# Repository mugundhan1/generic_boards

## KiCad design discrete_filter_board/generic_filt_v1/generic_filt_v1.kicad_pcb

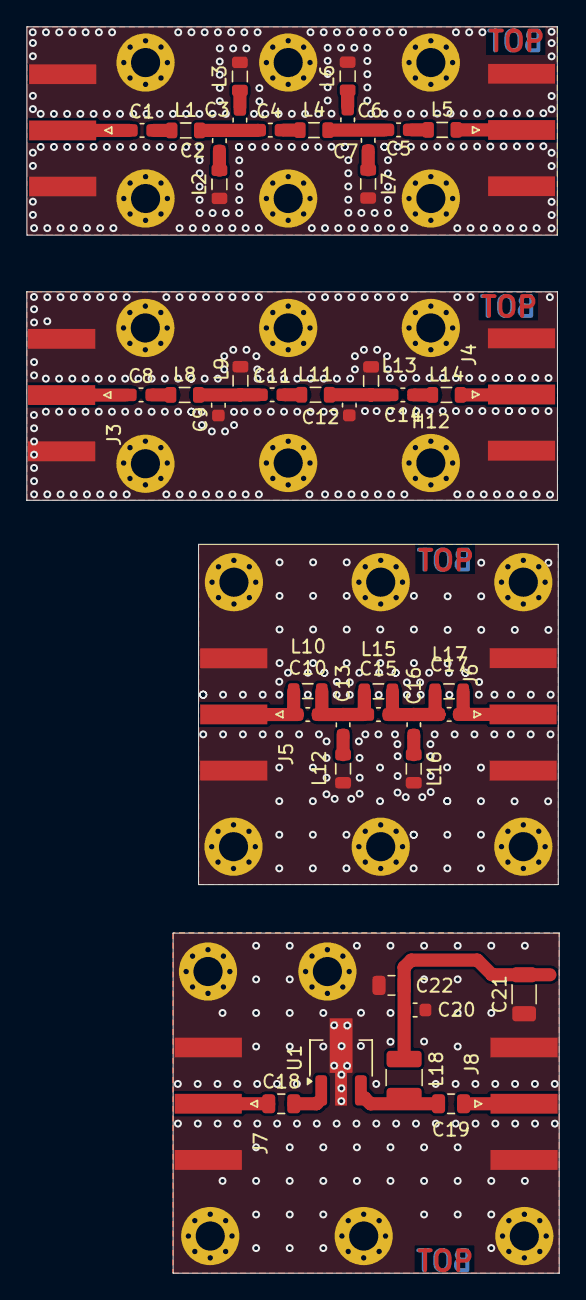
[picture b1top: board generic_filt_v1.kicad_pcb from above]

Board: 2 copper layers, 40.3 x 94.2 mm, 72 parts (0 on the bottom side), 30 nets.

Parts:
C1, C2, C3, C4, C5, C6, C7, C8, C9, C10, C11, C12, C13, C14, C15, C16, C17: C_Small; C_0603_1608Metric
C18, C19: 0.01 u; C_0805_2012Metric
C20: 0.1u; C_0603_1608Metric
C21: 10u; C_1206_3216Metric
C22: 1 u; C_0805_2012Metric
H1, H2, H3, H4, H5, H6, H7, H8, H9, H10, H11, H12, H13, H14, H15, H16, H17, H18, H19, H20, H21, H22, H23: MountingHole_Pad; MountingHole_2.2mm_M2_Pad_Via
J1, J2, J3, J4, J5, J6, J7, J8: Conn_Coaxial; SMA_Amphenol_132289_EdgeMount
L1, L2, L3, L4, L5, L6, L7, L8, L9, L10, L11, L12, L13, L14, L15, L16, L17: L_Small; L_0805_2012Metric
L18: 10 uH; L_1210_3225Metric
U1: PGA-103+; SOT-89-3_Handsoldering

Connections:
+5V: C20.2, C21.2, C22.2, L18.1
GND: C9.1, C12.1, C20.1, C21.1, C22.1, H1.1, H2.1, H3.1, H4.1, H5.1, H6.1, H7.1, H8.1, H9.1, H10.1, H11.1, H12.1, H13.1, H14.1, H15.1, H16.1, H17.1, H18.1, H19.1, H20.1, H21.1, H22.1, H23.1, J1.2 (Ext), J2.2 (Ext), J3.2 (Ext), J4.2 (Ext), J5.2 (Ext), J6.2 (Ext), J7.2 (Ext), J8.2 (Ext), L2.2, L3.2, L6.2, L7.2, L9.2, L12.2, L13.2, L16.2, U1.2 (GROUND)
unnamed: C1.2, L1.1
unnamed: C2.1, L2.1
unnamed: C2.2, C3.2, C4.1, L1.2
unnamed: C3.1, L3.1
unnamed: C4.2, L4.1
unnamed: C5.1, C6.2, C7.2, L4.2
unnamed: C5.2, L5.1
unnamed: C6.1, L6.1
unnamed: C7.1, L7.1
unnamed: C8.2, L8.1
unnamed: C10.2, C13.2, C15.1, L10.2, L15.1
unnamed: C9.2, C11.1, L8.2, L9.1
unnamed: C11.2, L11.1
unnamed: C12.2, C14.1, L11.2, L13.1
unnamed: C13.1, L12.1
unnamed: C14.2, L14.1
unnamed: C15.2, C16.2, C17.1, L15.2, L17.1
unnamed: C16.1, L16.1
unnamed: J1.1 (In), L5.2
unnamed: C1.1, J2.1 (In)
unnamed: C8.1, J3.1 (In)
unnamed: J4.1 (In), L14.2
unnamed: C10.1, J5.1 (In), L10.1
unnamed: C17.2, J6.1 (In), L17.2
unnamed: C18.1, J7.1 (In)
unnamed: C19.2, J8.1 (In)
unnamed: C18.2, U1.1 (RF-IN)
unnamed: C19.1, L18.2, U1.3 (RF-OUT/DC-IN)

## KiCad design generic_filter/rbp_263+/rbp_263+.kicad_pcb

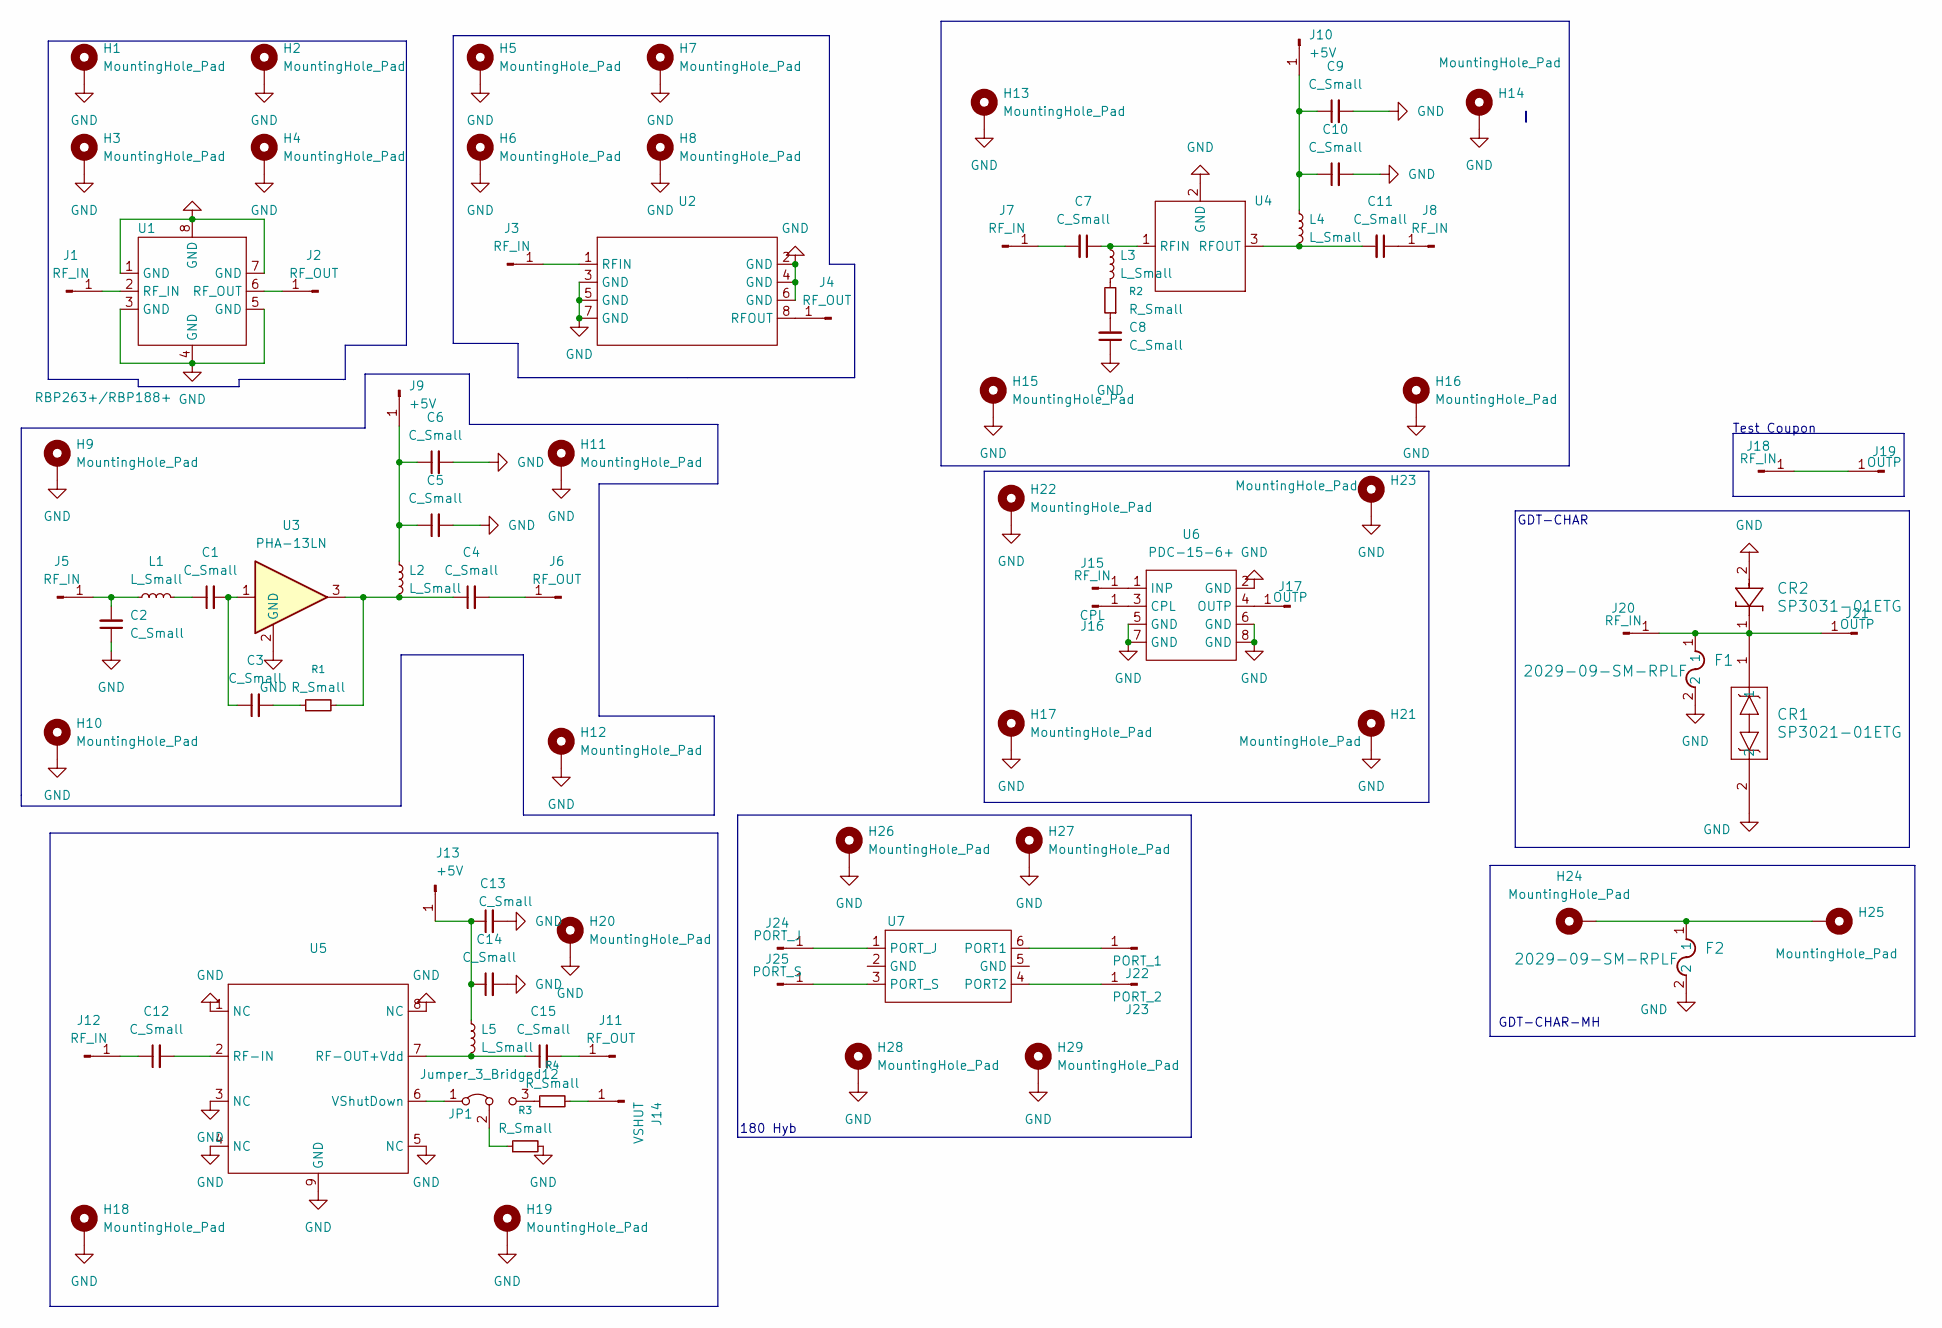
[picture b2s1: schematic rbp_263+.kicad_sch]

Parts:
C1, C2, C3, C4, C5, C7, C8, C10, C11, C12, C14, C15: C_Small; C_0603_1608Metric_Pad1.08x0.95mm_HandSolder
C6, C9, C13: C_Small; C_0805_2012Metric_Pad1.18x1.45mm_HandSolder
CR1: SP3021-01ETG; SOD882_LTF
CR2: SP3031-01ETG; SOD882_LTF-L
F1, F2: 2029-09-SM-RPLF; FUSE_2029-09-SM-RPLF_BRN
H1, H2, H3, H4, H5, H6, H7, H8, H9, H10, H11, H12, H13, H14, H15, H16, H17, H18, H19, H20, H21, H22, H23, H26, H27, H28, H29: MountingHole_Pad; MountingHole_2.2mm_M2_DIN965_Pad
H24, H25: MountingHole_Pad; MountingHole_2.7mm_M2.5_DIN965_Pad_TopBottom
J1, J3, J5, J7, J8, J12, J15, J18, J20: RF_IN; RF_SMA_Edge_PanelMount
J2, J4, J6, J11: RF_OUT; RF_SMA_Edge_PanelMount
J9, J10, J13: +5V; RF_SMA_Edge_PanelMount
J14: VSHUT; RF_SMA_Edge_PanelMount
J16: CPL; RF_SMA_Edge_PanelMount
J17, J19, J21: OUTP; RF_SMA_Edge_PanelMount
J22: PORT_1; RF_SMA_Edge_PanelMount
J23: PORT_2; RF_SMA_Edge_PanelMount
J24: PORT_J; RF_SMA_Edge_PanelMount
J25: PORT_S; RF_SMA_Edge_PanelMount
JP1: Jumper_3_Bridged12; PinHeader_1x03_P1.00mm_Vertical
L1, L3: L_Small; L_0603_1608Metric_Pad1.05x0.95mm_HandSolder
L2, L4, L5: L_Small; L_1210_3225Metric_Pad1.42x2.65mm_HandSolder
R1, R2, R3, R4: R_Small; R_0603_1608Metric_Pad0.98x0.95mm_HandSolder
U1: RBP263+/RBP188+; Mini-Circuits_GP731_LandPatternPL-176
U2: Mini-Circuits_HF1139_LandPatternPL-230
U3: PHA-13LN; SOT-89-3
U4: SOT-89-3_Handsoldering
U5: QFN-8_EP_2x2_Pitch0.5mm
U6: PDC-15-6+; Mini-Circuits_A01
U7: Mini-Circuits_CD636_H4.11mm

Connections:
GND: C2.1, C5.2, C6.2, C8.1, C9.2, C10.2, C13.2, C14.2, CR1.2, CR2.2, F1.2, F2.2, H1.1, H2.1, H3.1, H4.1, H5.1, H6.1, H7.1, H8.1, H9.1, H10.1, H11.1, H12.1, H13.1, H14.1, H15.1, H16.1, H17.1, H18.1, H19.1, H20.1, H21.1, H22.1, H23.1, H26.1, H27.1, H28.1, H29.1, R3.2, U1.1 (GND), U1.3 (GND), U1.4 (GND), U1.5 (GND), U1.7 (GND), U1.8 (GND), U2.2 (GND), U2.3 (GND), U2.4 (GND), U2.5 (GND), U2.6 (GND), U2.7 (GND), U3.2 (GND), U4.2 (GND), U5.1 (NC), U5.3 (NC), U5.4 (NC), U5.5 (NC), U5.8 (NC), U5.9 (GND), U6.2 (GND), U6.5 (GND), U6.6 (GND), U6.7 (GND), U6.8 (GND)
unnamed: C1.1, L1.2
unnamed: C1.2, C3.1, U3.1
unnamed: C3.2, R1.1
unnamed: C4.1, L2.2, R1.2, U3.3
unnamed: C8.2, R2.1
unnamed: F2.1, H24.1, H25.1
unnamed: J1.1, U1.2 (RF_IN)
unnamed: J2.1, U1.6 (RF_OUT)
unnamed: J3.1, U2.1 (RFIN)
unnamed: J4.1, U2.8 (RFOUT)
unnamed: C2.2, J5.1, L1.1
unnamed: C4.2, J6.1
unnamed: C7.2, J7.1
unnamed: C11.1, J8.1
unnamed: C5.1, C6.1, J9.1, L2.1
unnamed: C9.1, C10.1, J10.1, L4.1
unnamed: C15.2, J11.1
unnamed: C12.1, J12.1
unnamed: C13.1, C14.1, J13.1, L5.1
unnamed: J14.1, R4.2
unnamed: J15.1, U6.1 (INP)
unnamed: J16.1, U6.3 (CPL)
unnamed: J17.1, U6.4 (OUTP)
unnamed: J18.1, J19.1
unnamed: CR1.1, CR2.1, F1.1, J20.1, J21.1
unnamed: J22.1, U7.6 (PORT1)
unnamed: J23.1, U7.4 (PORT2)
unnamed: J24.1, U7.1 (PORT_J)
unnamed: J25.1, U7.3 (PORT_S)
unnamed: JP1.1 (A), U5.6 (VShutDown)
unnamed: JP1.3 (B), R4.1
unnamed: JP1.2 (C), R3.1
unnamed: L3.2, R2.2
unnamed: C7.1, L3.1, U4.1 (RFIN)
unnamed: C11.2, L4.2, U4.3 (RFOUT)
unnamed: C12.2, U5.2 (RF-IN)
unnamed: C15.1, L5.2, U5.7 (RF-OUT+Vdd)

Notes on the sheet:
GDT-CHAR-MH
Test Coupon
GDT-CHAR
180 Hyb

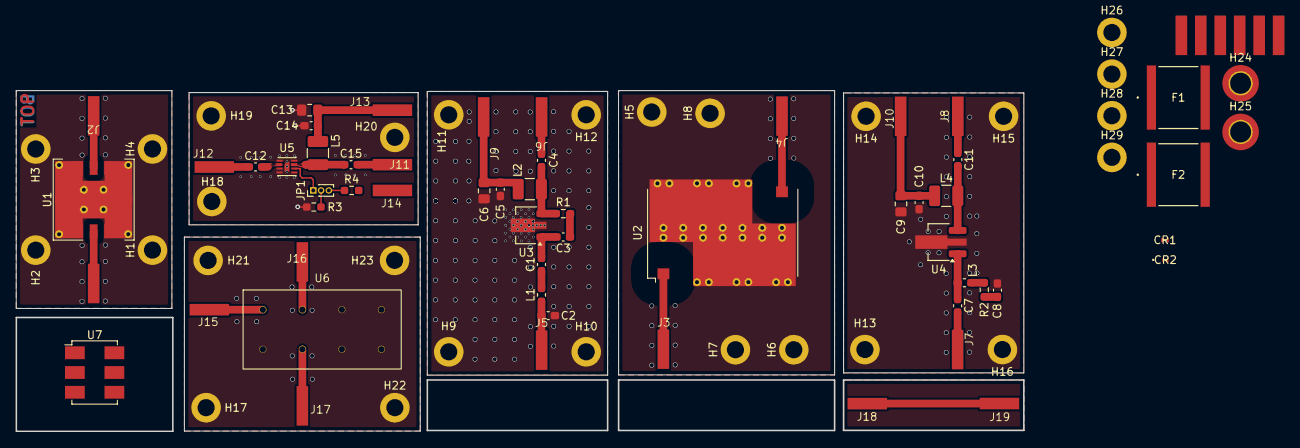
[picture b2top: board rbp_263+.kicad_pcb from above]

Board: 2 copper layers, 129.5 x 43.7 mm, 90 parts (0 on the bottom side), 38 nets.

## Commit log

2025-12-12 adding files
2025-12-29 updates on Dec 29, 2025
2026-01-01 included all amp ckts
2026-01-12 added gdt, tvs schematics and footprints
2026-01-19 Updated by jayasandhya
    via stitched,
    2 pcbs updated
    solder mask removed
    layout slightly changed for optimization
    mouse bits added - panelized
2026-02-17 updated -jayasandhya
2026-03-25 adding generic filter boards
2026-03-27 bpf design
2026-04-20 completed pcb routing
